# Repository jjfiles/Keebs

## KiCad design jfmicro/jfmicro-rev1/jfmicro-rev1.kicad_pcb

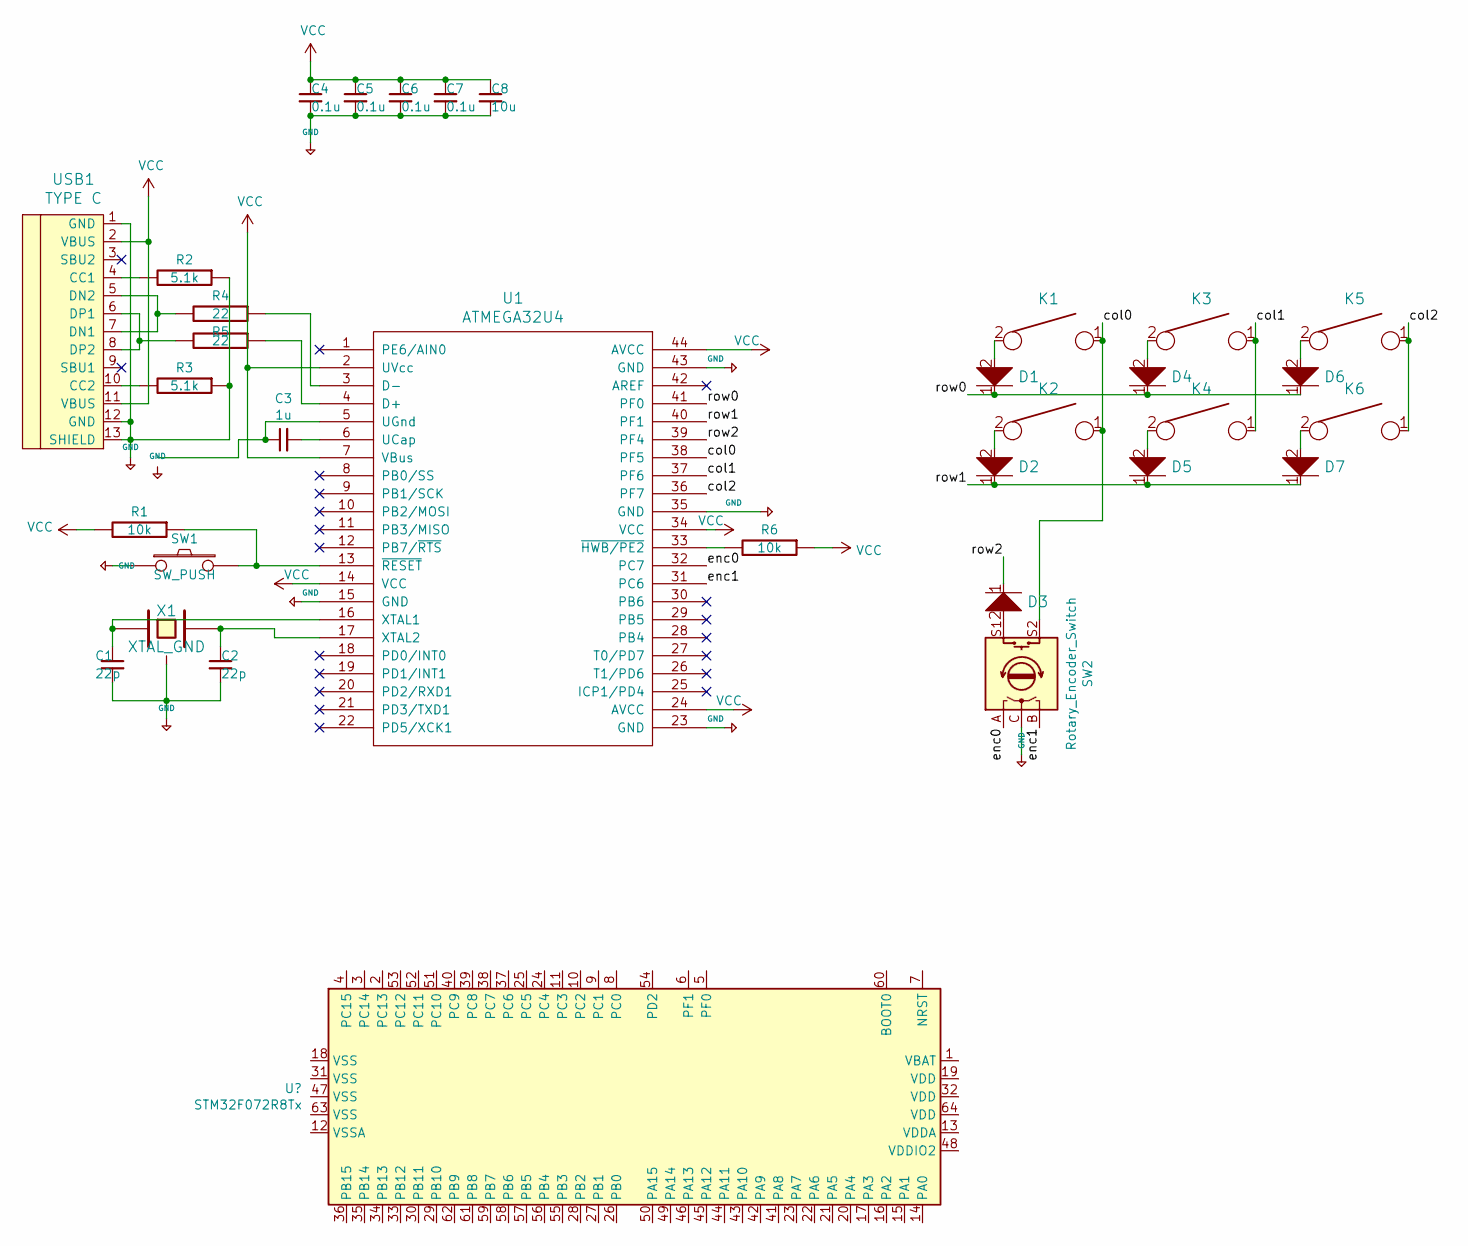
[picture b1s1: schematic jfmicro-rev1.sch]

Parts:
C1, C2: 22p; C_0805_2012Metric
C3: 1u; C_0805_2012Metric
C4, C5, C6, C7: 0.1u; C_0805_2012Metric
C8: 10u; C_0805_2012Metric
D1, D2, D3, D4, D5, D6, D7: D; D_0805_2012Metric
K1, K2, K3, K4, K5, K6: KEYSW; MXOnly-1U-Hotswap
R1, R6: 10k; R_0805_2012Metric
R2, R3: 5.1k; R_0805_2012Metric
R4, R5: 22; R_0805_2012Metric
SW1: SW_PUSH; SW_SPST_TL3342
SW2: Rotary_Encoder_Switch; RotaryEncoder_Alps_EC11E-Switch_Vertical_H20mm
U1: ATMEGA32U4; ATMEGA32U4-AU
USB1: TYPE C; HRO-TYPE-C-31-M-12
X1: XTAL_GND; Crystal_SMD_3225-4Pin_3.2x2.5mm

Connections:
+5V: C1.2, C2.2, C4.2, C5.2, C6.2, C7.2, C8.2, R2.1, R3.1, SW1.1, SW2.C, U1.15 (GND), U1.23 (GND), U1.35 (GND), U1.43 (GND), USB1.1 (GND), USB1.12 (GND), USB1.13 (SHIELD), X1.3
/col0: K1.1, K2.1, SW2.S2, U1.38 (PF5)
/col1: K3.1, K4.1, U1.37 (PF6)
/col2: K5.1, K6.1, U1.36 (PF7)
/enc0: SW2.A, U1.32 (PC7)
/enc1: SW2.B, U1.31 (PC6)
/row0: D1.1, D4.1, D6.1, U1.41 (PF0)
/row1: D2.1, D5.1, D7.1, U1.40 (PF1)
/row2: D3.1, U1.39 (PF4)
unnamed: C1.1, U1.16 (XTAL1), X1.1
unnamed: C2.1, U1.17 (XTAL2), X1.2
unnamed: C3.1, U1.5 (UGnd)
unnamed: C3.2, U1.6 (UCap)
unnamed: D1.2, K1.2
unnamed: D2.2, K2.2
unnamed: D3.2, SW2.S1
unnamed: D4.2, K3.2
unnamed: D5.2, K4.2
unnamed: D6.2, K5.2
unnamed: D7.2, K6.2
unnamed: R1.1, SW1.2, U1.13 (~RESET)
unnamed: R2.2, USB1.4 (CC1)
unnamed: R3.2, USB1.10 (CC2)
unnamed: R4.1, U1.3 (D-)
unnamed: R4.2, USB1.5 (DN2), USB1.7 (DN1)
unnamed: R5.1, U1.4 (D+)
unnamed: R5.2, USB1.6 (DP1), USB1.8 (DP2)
unnamed: R6.2, U1.33 (~HWB/PE2)
VCC: C4.1, C5.1, C6.1, C7.1, C8.1, R1.2, R6.1, U1.2 (UVcc), U1.7 (VBus), U1.14 (VCC), U1.24 (AVCC), U1.34 (VCC), U1.44 (AVCC), USB1.2 (VBUS), USB1.11 (VBUS)

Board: 2 copper layers, 32 parts (0 on the bottom side), 29 nets, no tracks yet.

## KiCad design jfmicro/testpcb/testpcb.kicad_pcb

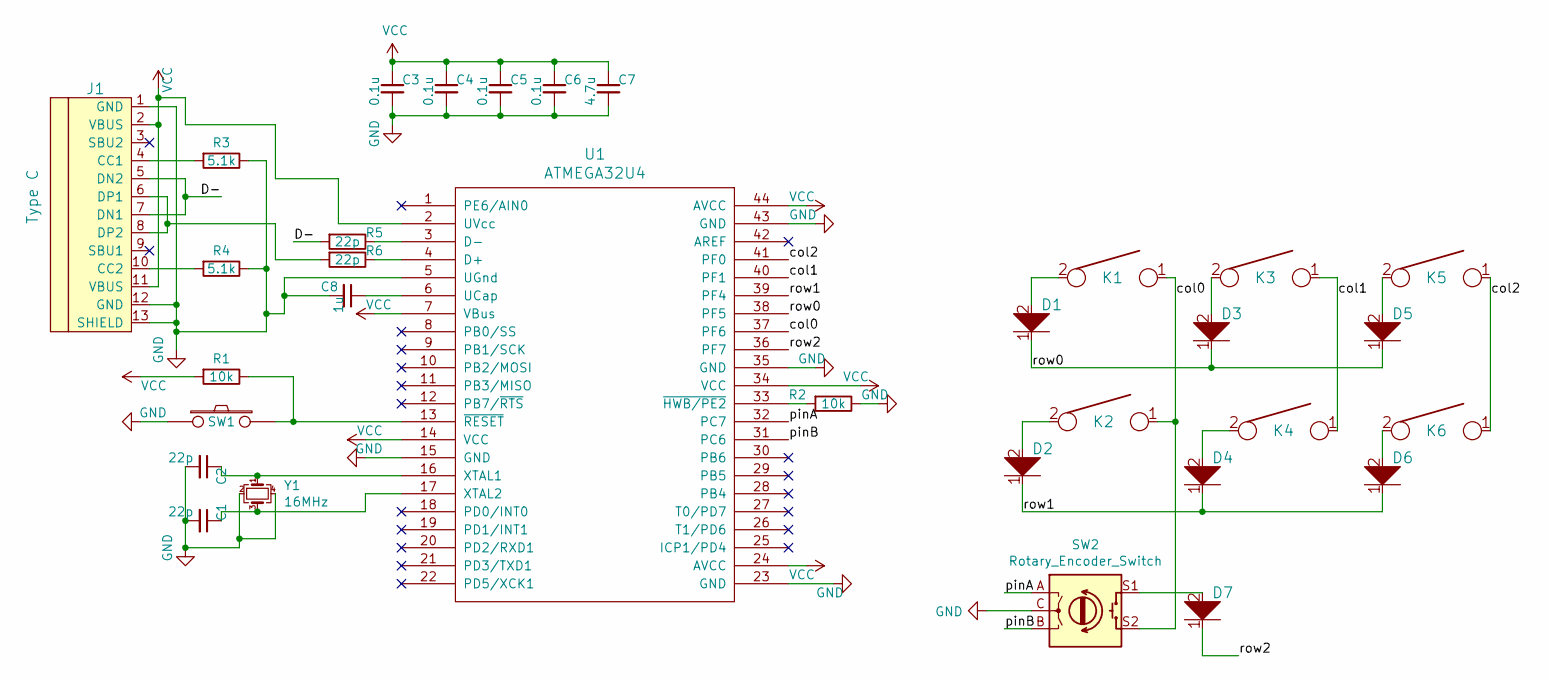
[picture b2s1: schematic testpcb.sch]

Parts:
C1, C2: 22p; C_0805_2012Metric
C3, C4, C5, C6: 0.1u; C_0805_2012Metric
C7: 4.7u; C_0805_2012Metric
C8: 1u; C_0805_2012Metric
D1, D2, D3, D4, D5, D6, D7: D; D_SOD123_axial
J1: Type C; 12401598E4#2A
K1, K2, K3, K4, K5, K6: KEYSW; MXOnly-1U-Hotswap
R1, R2: 10k; R_0805_2012Metric
R3, R4: 5.1k; R_0805_2012Metric
R5, R6: 22p; R_0805_2012Metric
SW1: SW_PUSH; SW_SPST_TL3342
SW2: Rotary_Encoder_Switch; RotaryEncoder_Alps_EC11E-Switch_Vertical_H20mm
U1: ATMEGA32U4; TQFP-44_10x10mm_P0.8mm
Y1: 16MHz; Crystal_SMD_3225-4Pin_3.2x2.5mm

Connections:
/D-: J1.5 (DN2), J1.7 (DN1), R5.2
/col0: K1.1, K2.1, SW2.S2, U1.37 (PF6)
/col1: K3.1, K4.1, U1.40 (PF1)
/col2: K5.1, K6.1, U1.41 (PF0)
/pinA: SW2.A, U1.32 (PC7)
/pinB: SW2.B, U1.31 (PC6)
/row0: D1.1, D3.1, D5.1, U1.38 (PF5)
/row1: D2.1, D4.1, D6.1, U1.39 (PF4)
/row2: D7.1, U1.36 (PF7)
GND: C1.2, C2.2, C3.2, C4.2, C5.2, C6.2, C7.2, C8.2, J1.1 (GND), J1.12 (GND), J1.13 (SHIELD), R2.1, R3.1, R4.1, SW1.1, SW2.C, U1.5 (UGnd), U1.15 (GND), U1.23 (GND), U1.35 (GND), U1.43 (GND), Y1.2, Y1.4
unnamed: C1.1, U1.17 (XTAL2), Y1.3
unnamed: C2.1, U1.16 (XTAL1), Y1.1
unnamed: C8.1, U1.6 (UCap)
unnamed: D1.2, K1.2
unnamed: D2.2, K2.2
unnamed: D3.2, K3.2
unnamed: D4.2, K4.2
unnamed: D5.2, K5.2
unnamed: D6.2, K6.2
unnamed: D7.2, SW2.S1
unnamed: J1.4 (CC1), R3.2
unnamed: J1.6 (DP1), J1.8 (DP2), R6.2
unnamed: J1.10 (CC2), R4.2
unnamed: R1.1, SW1.2, U1.13 (~RESET)
unnamed: R2.2, U1.33 (~HWB/PE2)
unnamed: R5.1, U1.3 (D-)
unnamed: R6.1, U1.4 (D+)
VCC: C3.1, C4.1, C5.1, C6.1, C7.1, J1.2 (VBUS), J1.11 (VBUS), R1.2, U1.2 (UVcc), U1.7 (VBus), U1.14 (VCC), U1.24 (AVCC), U1.34 (VCC), U1.44 (AVCC)

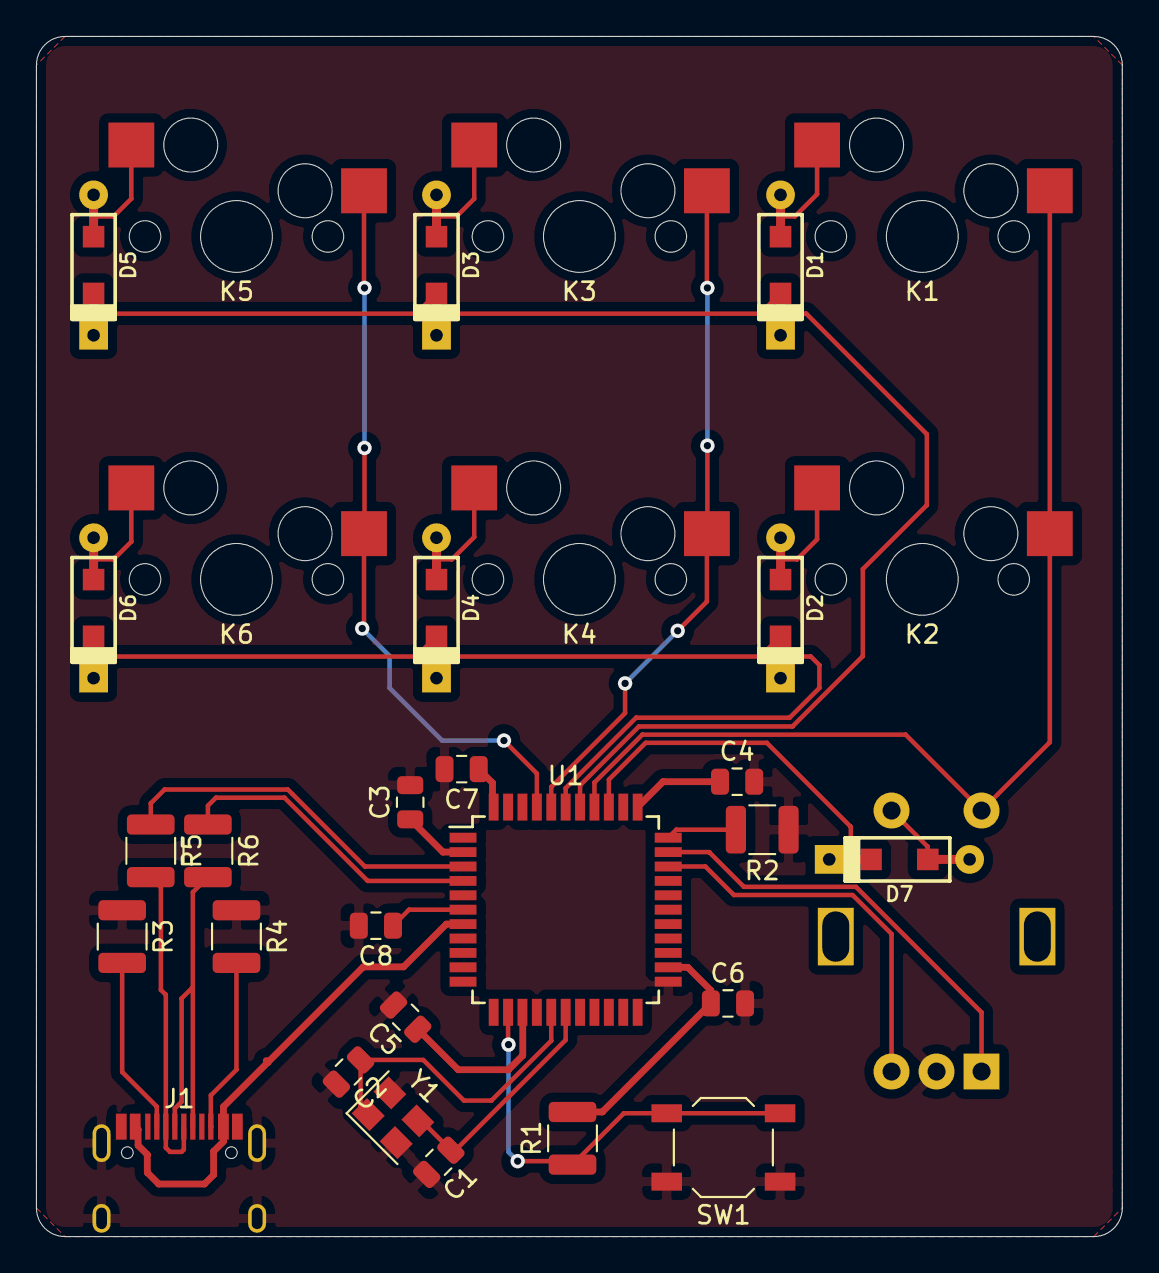
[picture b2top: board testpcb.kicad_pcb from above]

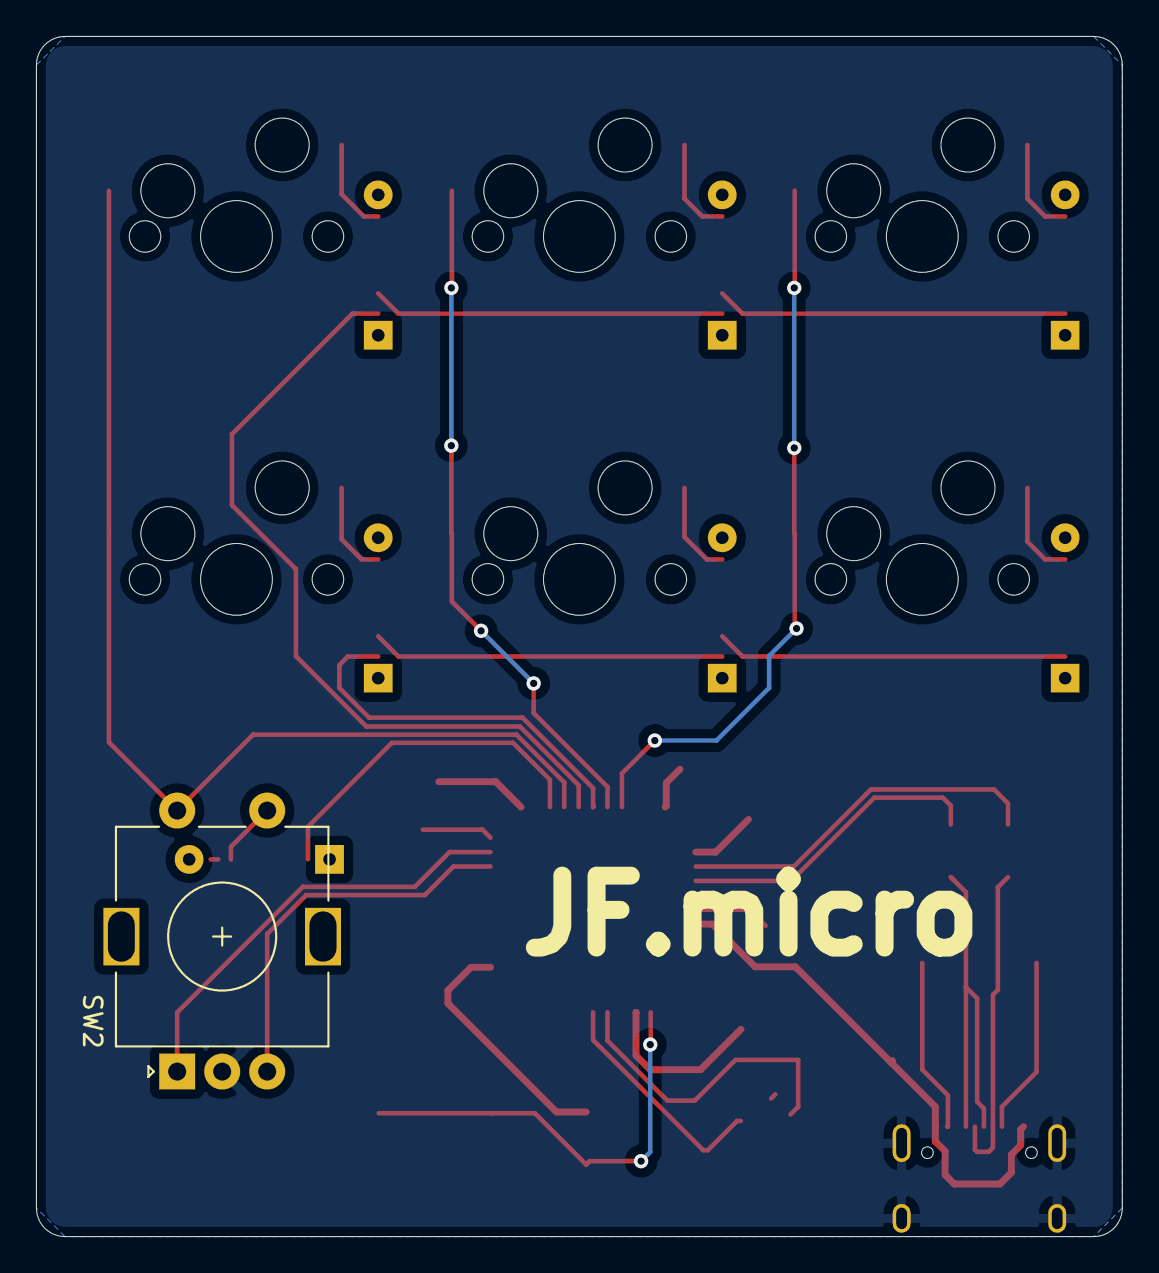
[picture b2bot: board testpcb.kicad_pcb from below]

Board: 2 copper layers, 60.3 x 66.7 mm, 32 parts (7 on the bottom side), 28 nets.

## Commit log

2020-11-24 initla commit
2021-03-31 micro revision two and more comps
2022-02-11 added attributes file
